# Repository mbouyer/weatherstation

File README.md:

# weatherstation
A home weather station with internet connectivity

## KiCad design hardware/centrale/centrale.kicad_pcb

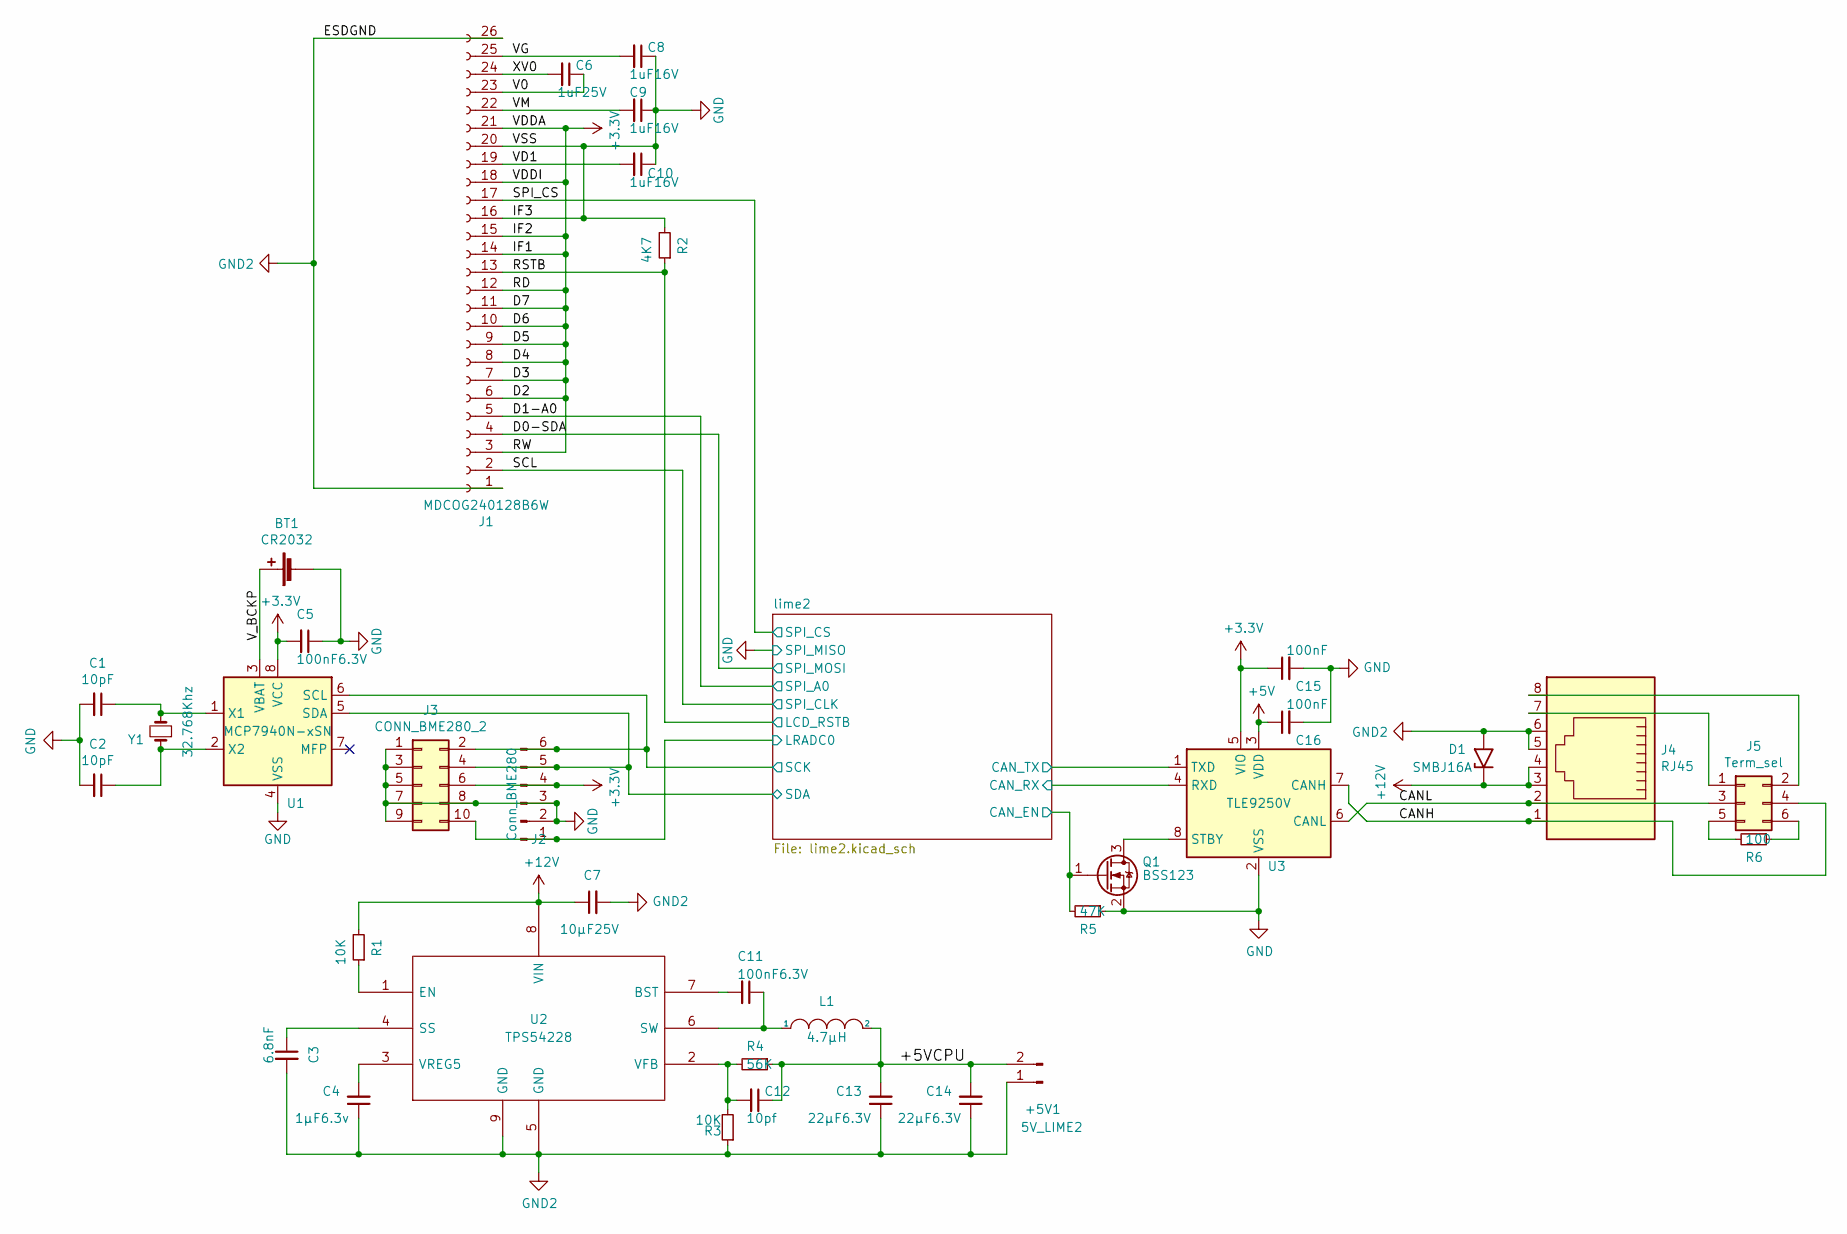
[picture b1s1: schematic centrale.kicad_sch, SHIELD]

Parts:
+5V1: 5V_LIME2; MC24356
BT1: CR2032; 1066
C1, C2: 10pF; C_0603_1608Metric_Pad1.08x0.95mm_HandSolder
C3: 6.8nF; C_0603_1608Metric_Pad1.08x0.95mm_HandSolder
C4: 1µF6.3v; C_0805_2012Metric_Pad1.18x1.45mm_HandSolder
C5, C11: 100nF6.3V; C_0805_2012Metric_Pad1.18x1.45mm_HandSolder
C6: 1uF25V; C_0805_2012Metric_Pad1.18x1.45mm_HandSolder
C7: 10µF25V; C_1210_3225Metric_Pad1.33x2.70mm_HandSolder
C8, C9, C10: 1uF16V; C_0805_2012Metric_Pad1.18x1.45mm_HandSolder
C12: 10pf; C_0603_1608Metric_Pad1.08x0.95mm_HandSolder
C13, C14: 22µF6.3V; C_1210_3225Metric_Pad1.33x2.70mm_HandSolder
C15, C16: 100nF; C_0805_2012Metric_Pad1.18x1.45mm_HandSolder
D1: SMBJ16A; D_SMB_Handsoldering
J1: MDCOG240128B6W; multicomp505110-2691
J2: Conn_BME280; JST_S6B-ZR-SM4A-TF(LF)(SN)
J3: CONN_BME280_2; CONN-TE-MICROMATCH-5X2-PTH-BOSS
J4: RJ45; RJ45_Amphenol_54602-x08_Horizontal
J5: Term_sel; PinHeader_2x03_P2.54mm_Vertical
L1: 4.7µH; L_TT_7.3x6.8
Q1: BSS123; SOT-23
R1, R3: 10K; R_1206_3216Metric_Pad1.30x1.75mm_HandSolder
R2: 4K7; R_0805_2012Metric_Pad1.20x1.40mm_HandSolder
R4: 56K; R_0805_2012Metric_Pad1.20x1.40mm_HandSolder
R5: 47K; R_0805_2012Metric_Pad1.20x1.40mm_HandSolder
R6: 100; R_0805_2012Metric_Pad1.20x1.40mm_HandSolder
U1: MCP7940N-xSN; SOIC-8_3.9x4.9mm_P1.27mm
U2: TPS54228; SOIC-8-1EP_3.9x4.9mm_P1.27mm_EP2.41x3.3mm
U3: TLE9250V; SOIC-8_3.9x4.9mm_P1.27mm
Y1: 32.768Khz; CMR200T

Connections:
+3.3V: C5.2, C15.1, J1.3, J1.6, J1.7, J1.8, J1.9, J1.10, J1.11, J1.12, J1.14, J1.15, J1.18, J1.21, J2.4, J3.6, U1.8 (VCC), U3.5 (VIO); also elsewhere on the board
+5V: C16.1, U3.3 (VDD); also elsewhere on the board
+12V: C7.1, D1.1 (A1), J4.3, J4.4, R1.2, U2.8 (VIN)
/+5VCPU: +5V1.2, C12.1, C13.2, C14.2, L1.2, R4.1
/CANH: J4.1, J5.4, U3.7 (CANH)
/CANL: J4.2, J5.3, U3.6 (CANL)
/D0-SDA: J1.4; also elsewhere on the board
/D1-A0: J1.5; also elsewhere on the board
/RSTB: J1.13, R2.1; also elsewhere on the board
/SCL: J1.2; also elsewhere on the board
/SPI_CS: J1.17; also elsewhere on the board
/V0: C6.1, J1.23
/VD1: C10.2, J1.19
/VG: C8.2, J1.25
/VM: C9.2, J1.22
/V_BCKP: BT1.1 (+), U1.3 (VBAT)
/XV0: C6.2, J1.24
/lime2/EMDC/LCD1_D21/ATADREQ/CAN_RX/EINT21/CSI1_D21/PH21: U3.4 (RXD); also elsewhere on the board
/lime2/ERXDV/LCD1_D20/ATAOE/CAN_TX/EINT20/CSI1_D20/PH20: U3.1 (TXD); also elsewhere on the board
/lime2/ERXERR/LCD1_D19/ATAD15/KP_OUT1/SMC_SDA/EINT19/CSI1_D19/PH19: Q1.1 (G), R5.2; also elsewhere on the board
/lime2/LRADC0: J2.1, J3.10; also elsewhere on the board
/lime2/TWI1_SCK/PB18: J2.6, J3.2, U1.6 (SCL); also elsewhere on the board
/lime2/TWI1_SDA/PB19: J2.5, J3.4, U1.5 (SDA); also elsewhere on the board
GND: BT1.2 (-), C1.2, C2.2, C5.1, C8.1, C9.1, C10.1, C15.2, C16.2, J1.16, J1.20, J2.2, J2.3, J3.1, J3.3, J3.5, J3.7, J3.8, J3.9, Q1.2 (S), R2.2, R5.1, U1.4 (VSS), U3.2 (VSS), U3.9 (VSS); also elsewhere on the board
GND2: +5V1.1, C3.2, C4.1, C7.2, C13.1, C14.1, D1.2 (A2), J1.1, J1.26, J4.5, J4.6, R3.1, U2.5 (GND), U2.9 (GND)
unnamed: C1.1, U1.1 (X1), Y1.2
unnamed: C2.1, U1.2 (X2), Y1.1
unnamed: C3.1, U2.4 (SS)
unnamed: C4.2, U2.3 (VREG5)
unnamed: C11.1, L1.1, U2.6 (SW)
unnamed: C11.2, U2.7 (BST)
unnamed: C12.2, R3.2, R4.2, U2.2 (VFB)
unnamed: J4.7, J5.1
unnamed: J4.8, J5.2
unnamed: J5.5, R6.2
unnamed: J5.6, R6.1
unnamed: Q1.3 (D), U3.8 (STBY)
unnamed: R1.1, U2.1 (EN)

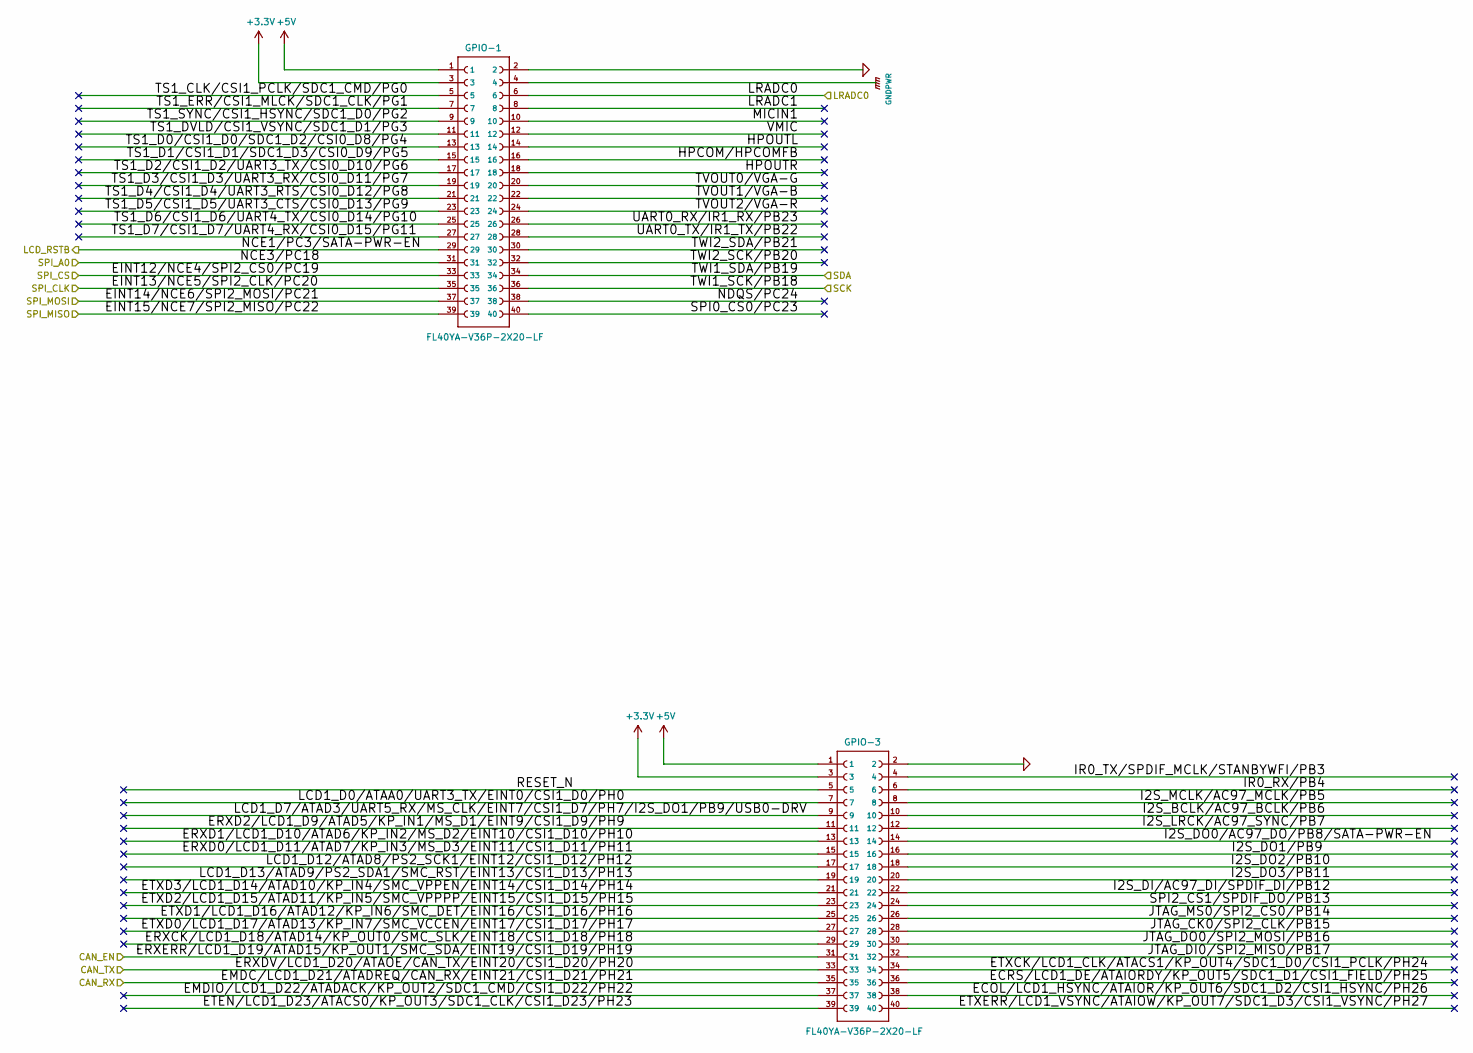
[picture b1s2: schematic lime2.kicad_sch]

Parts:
GPIO-1, GPIO-3: FL40YA-V36P-2X20-LF; A20_OLIMEXINO_LIME2_SHIELD_1-YA-V36P-2X20-LF

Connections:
+3.3V: GPIO-1.3, GPIO-3.3; also elsewhere on the board
+5V: GPIO-1.1, GPIO-3.1; also elsewhere on the board
/D0-SDA: GPIO-1.37; also elsewhere on the board
/D1-A0: GPIO-1.31; also elsewhere on the board
/RSTB: GPIO-1.29; also elsewhere on the board
/SCL: GPIO-1.35; also elsewhere on the board
/SPI_CS: GPIO-1.33; also elsewhere on the board
/lime2/ECOL/LCD1_HSYNC/ATAIOR/KP_OUT6/SDC1_D2/CSI1_HSYNC/PH26: GPIO-3.38
/lime2/ECRS/LCD1_DE/ATAIORDY/KP_OUT5/SDC1_D1/CSI1_FIELD/PH25: GPIO-3.36
/lime2/EMDC/LCD1_D21/ATADREQ/CAN_RX/EINT21/CSI1_D21/PH21: GPIO-3.35; also elsewhere on the board
/lime2/EMDIO/LCD1_D22/ATADACK/KP_OUT2/SDC1_CMD/CSI1_D22/PH22: GPIO-3.37
/lime2/ERXCK/LCD1_D18/ATAD14/KP_OUT0/SMC_SLK/EINT18/CSI1_D18/PH18: GPIO-3.29
/lime2/ERXD0/LCD1_D11/ATAD7/KP_IN3/MS_D3/EINT11/CSI1_D11/PH11: GPIO-3.15
/lime2/ERXD1/LCD1_D10/ATAD6/KP_IN2/MS_D2/EINT10/CSI1_D10/PH10: GPIO-3.13
/lime2/ERXD2/LCD1_D9/ATAD5/KP_IN1/MS_D1/EINT9/CSI1_D9/PH9: GPIO-3.11
/lime2/ERXDV/LCD1_D20/ATAOE/CAN_TX/EINT20/CSI1_D20/PH20: GPIO-3.33; also elsewhere on the board
/lime2/ERXERR/LCD1_D19/ATAD15/KP_OUT1/SMC_SDA/EINT19/CSI1_D19/PH19: GPIO-3.31; also elsewhere on the board
/lime2/ETEN/LCD1_D23/ATACS0/KP_OUT3/SDC1_CLK/CSI1_D23/PH23: GPIO-3.39
/lime2/ETXCK/LCD1_CLK/ATACS1/KP_OUT4/SDC1_D0/CSI1_PCLK/PH24: GPIO-3.34
/lime2/ETXD0/LCD1_D17/ATAD13/KP_IN7/SMC_VCCEN/EINT17/CSI1_D17/PH17: GPIO-3.27
/lime2/ETXD1/LCD1_D16/ATAD12/KP_IN6/SMC_DET/EINT16/CSI1_D16/PH16: GPIO-3.25
/lime2/ETXD2/LCD1_D15/ATAD11/KP_IN5/SMC_VPPPP/EINT15/CSI1_D15/PH15: GPIO-3.23
/lime2/ETXD3/LCD1_D14/ATAD10/KP_IN4/SMC_VPPEN/EINT14/CSI1_D14/PH14: GPIO-3.21
/lime2/ETXERR/LCD1_VSYNC/ATAIOW/KP_OUT7/SDC1_D3/CSI1_VSYNC/PH27: GPIO-3.40
/lime2/HPCOM/HPCOMFB: GPIO-1.16
/lime2/HPOUTL: GPIO-1.14
/lime2/HPOUTR: GPIO-1.18
/lime2/I2S_BCLK/AC97_BCLK/PB6: GPIO-3.10
/lime2/I2S_DI/AC97_DI/SPDIF_DI/PB12: GPIO-3.22
/lime2/I2S_DO0/AC97_DO/PB8/SATA-PWR-EN: GPIO-3.14
/lime2/I2S_DO1/PB9: GPIO-3.16
/lime2/I2S_DO2/PB10: GPIO-3.18
/lime2/I2S_DO3/PB11: GPIO-3.20
/lime2/I2S_LRCK/AC97_SYNC/PB7: GPIO-3.12
/lime2/I2S_MCLK/AC97_MCLK/PB5: GPIO-3.8
/lime2/IR0_RX/PB4: GPIO-3.6
/lime2/IR0_TX/SPDIF_MCLK/STANBYWFI/PB3: GPIO-3.4
/lime2/JTAG_CK0/SPI2_CLK/PB15: GPIO-3.28
/lime2/JTAG_DI0/SPI2_MISO/PB17: GPIO-3.32
/lime2/JTAG_DO0/SPI2_MOSI/PB16: GPIO-3.30
/lime2/JTAG_MS0/SPI2_CS0/PB14: GPIO-3.26
/lime2/LCD1_D0/ATAA0/UART3_TX/EINT0/CSI1_D0/PH0: GPIO-3.7
/lime2/LCD1_D7/ATAD3/UART5_RX/MS_CLK/EINT7/CSI1_D7/PH7/I2S_DO1/PB9/USB0-DRV: GPIO-3.9
/lime2/LCD1_D12/ATAD8/PS2_SCK1/EINT12/CSI1_D12/PH12: GPIO-3.17
/lime2/LCD1_D13/ATAD9/PS2_SDA1/SMC_RST/EINT13/CSI1_D13/PH13: GPIO-3.19
/lime2/LRADC0: GPIO-1.6; also elsewhere on the board
/lime2/LRADC1: GPIO-1.8
/lime2/MICIN1: GPIO-1.10
/lime2/NDQS/PC24: GPIO-1.38
/lime2/RESET_N: GPIO-3.5
/lime2/SPI0_CS0/PC23: GPIO-1.40
/lime2/SPI2_CS1/SPDIF_DO/PB13: GPIO-3.24
/lime2/TS1_CLK/CSI1_PCLK/SDC1_CMD/PG0: GPIO-1.5
/lime2/TS1_D0/CSI1_D0/SDC1_D2/CSI0_D8/PG4: GPIO-1.13
/lime2/TS1_D1/CSI1_D1/SDC1_D3/CSI0_D9/PG5: GPIO-1.15
/lime2/TS1_D2/CSI1_D2/UART3_TX/CSI0_D10/PG6: GPIO-1.17
/lime2/TS1_D3/CSI1_D3/UART3_RX/CSI0_D11/PG7: GPIO-1.19
/lime2/TS1_D4/CSI1_D4/UART3_RTS/CSI0_D12/PG8: GPIO-1.21
/lime2/TS1_D5/CSI1_D5/UART3_CTS/CSI0_D13/PG9: GPIO-1.23
/lime2/TS1_D6/CSI1_D6/UART4_TX/CSI0_D14/PG10: GPIO-1.25
/lime2/TS1_D7/CSI1_D7/UART4_RX/CSI0_D15/PG11: GPIO-1.27
/lime2/TS1_DVLD/CSI1_VSYNC/SDC1_D1/PG3: GPIO-1.11
/lime2/TS1_ERR/CSI1_MLCK/SDC1_CLK/PG1: GPIO-1.7
/lime2/TS1_SYNC/CSI1_HSYNC/SDC1_D0/PG2: GPIO-1.9
/lime2/TVOUT0/VGA-G: GPIO-1.20
/lime2/TVOUT1/VGA-B: GPIO-1.22
/lime2/TVOUT2/VGA-R: GPIO-1.24
/lime2/TWI1_SCK/PB18: GPIO-1.36; also elsewhere on the board
/lime2/TWI1_SDA/PB19: GPIO-1.34; also elsewhere on the board
/lime2/TWI2_SCK/PB20: GPIO-1.32
/lime2/TWI2_SDA/PB21: GPIO-1.30
/lime2/UART0_RX/IR1_RX/PB23: GPIO-1.26
/lime2/UART0_TX/IR1_TX/PB22: GPIO-1.28
/lime2/VMIC: GPIO-1.12
GND: GPIO-1.2, GPIO-1.39, GPIO-3.2; also elsewhere on the board
GNDPWR: GPIO-1.4

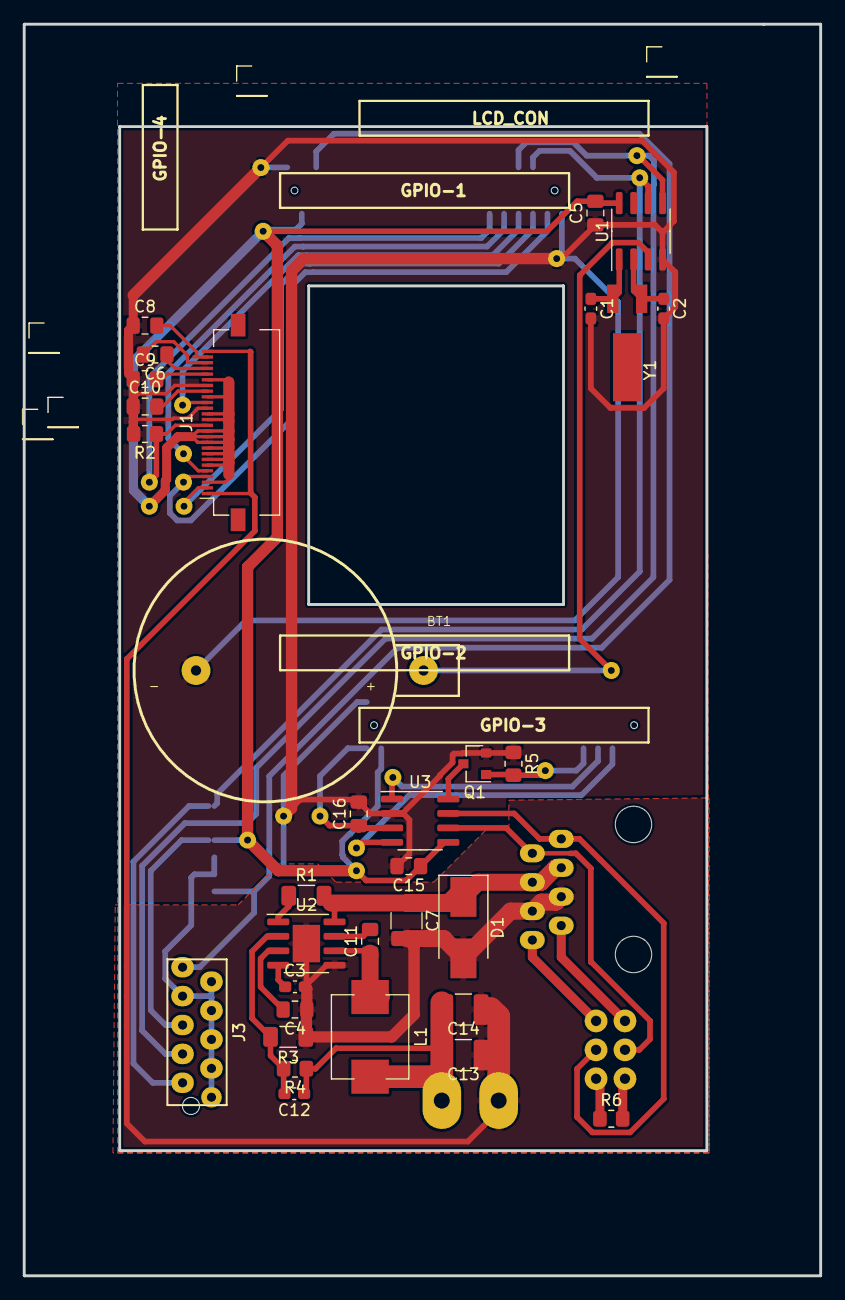
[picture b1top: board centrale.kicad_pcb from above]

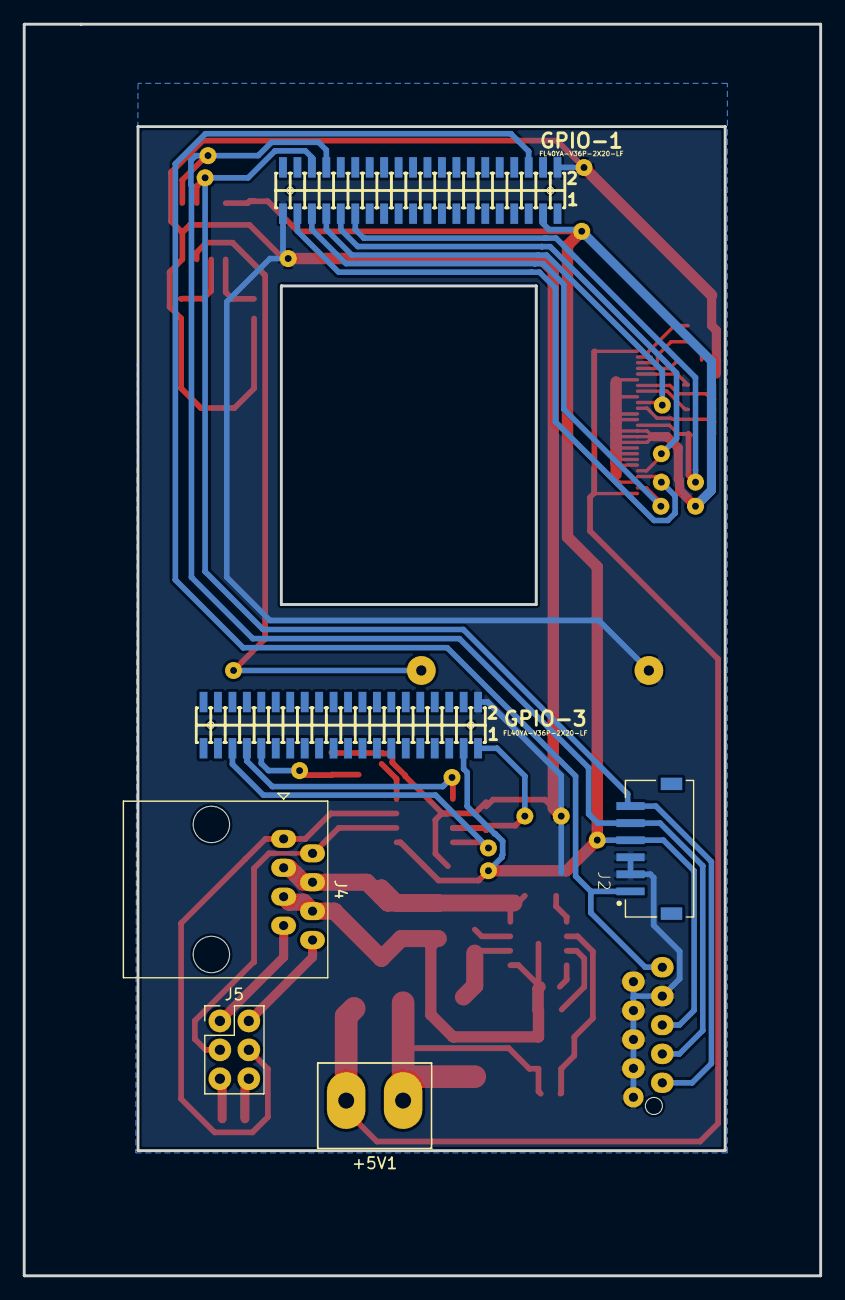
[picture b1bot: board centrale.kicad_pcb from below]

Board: 2 copper layers, 70.0 x 110.0 mm, 38 parts (6 on the bottom side), 38 nets.

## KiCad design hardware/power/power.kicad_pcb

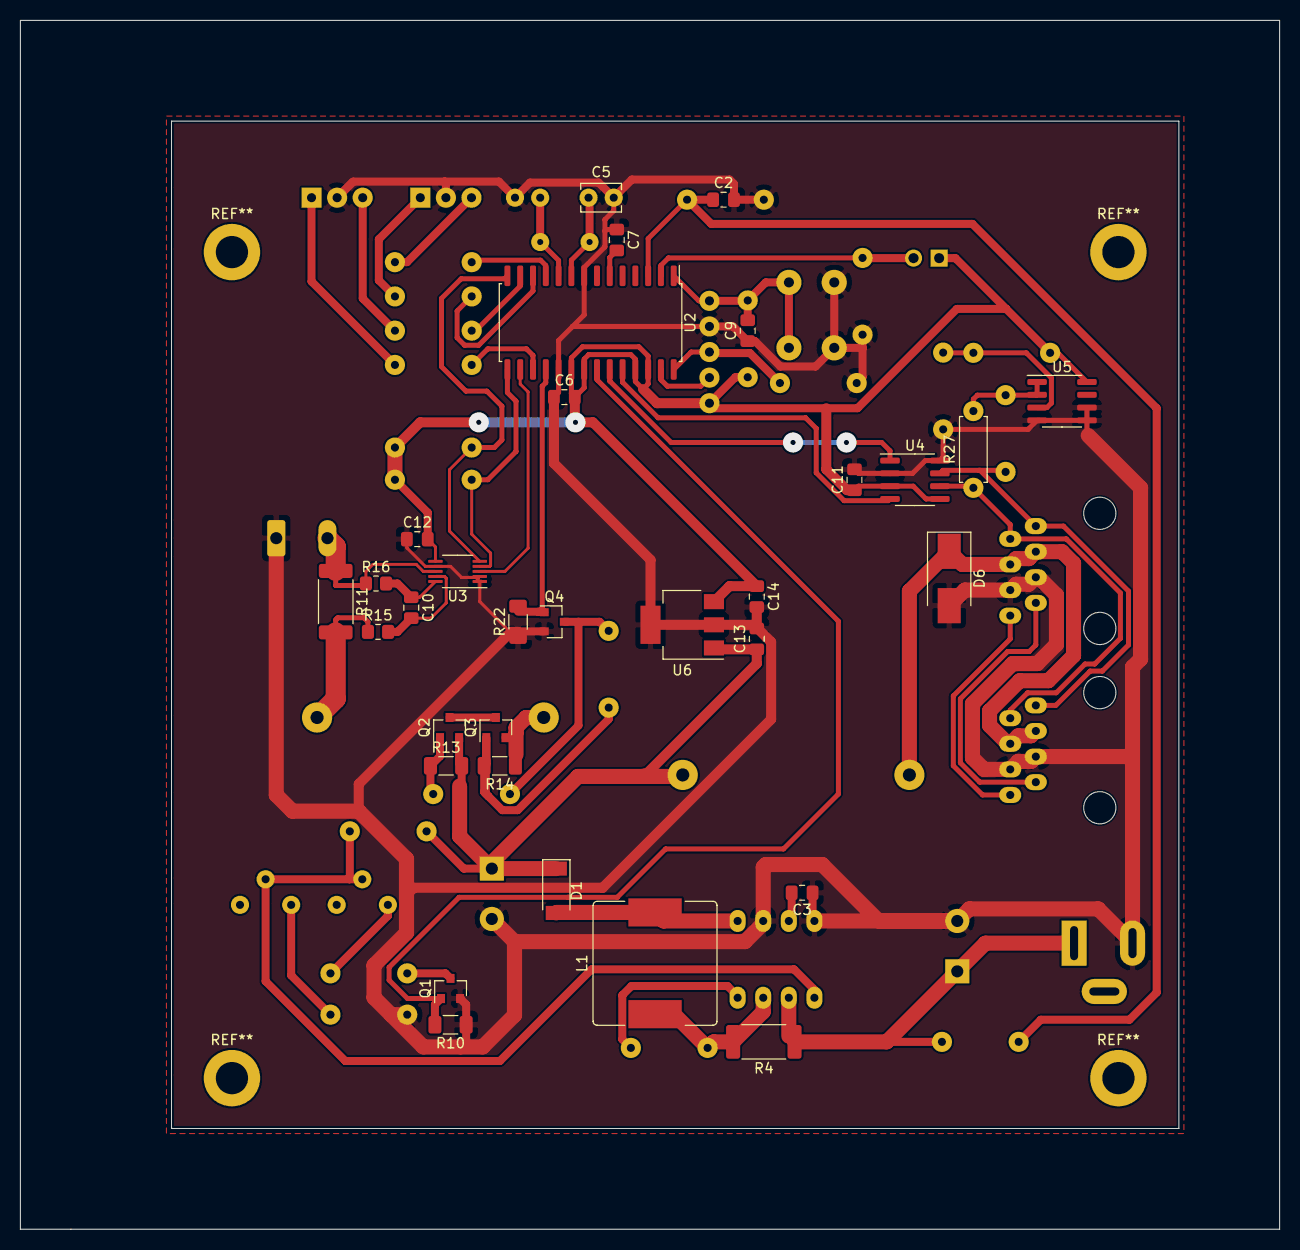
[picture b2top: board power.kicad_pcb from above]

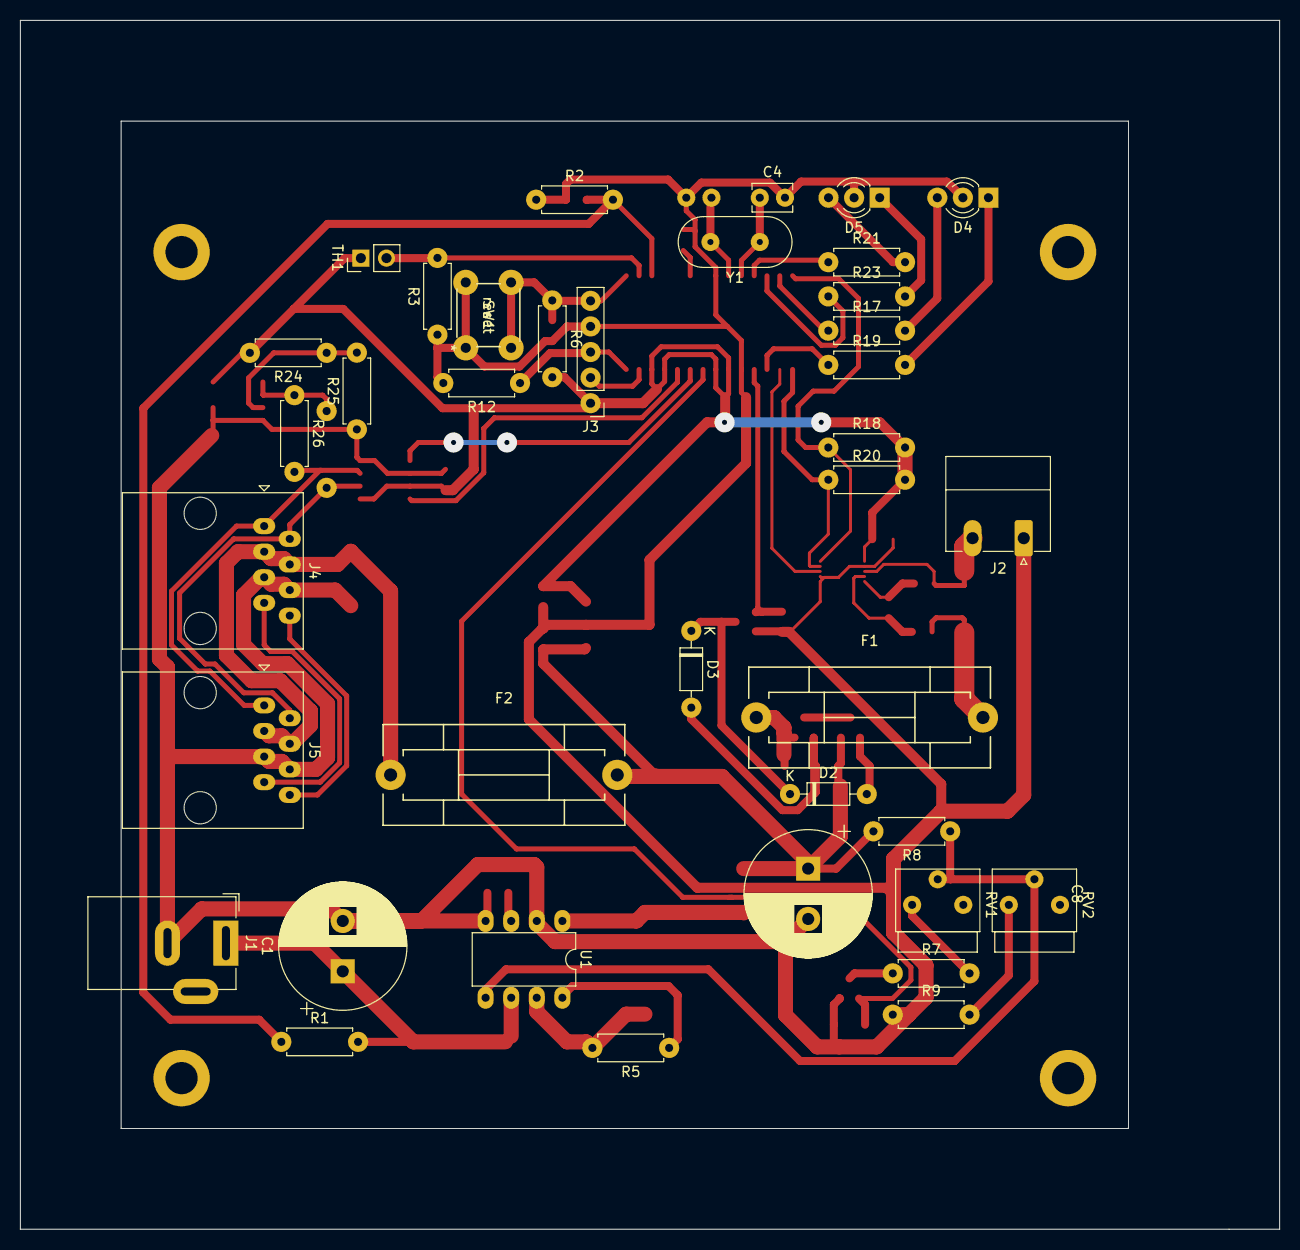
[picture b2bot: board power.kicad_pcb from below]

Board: 2 copper layers, 125.0 x 120.0 mm, 70 parts (38 on the bottom side), 51 nets.

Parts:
C1, C8: 1000µF; CP_Radial_D12.5mm_P5.00mm
C2, C6, C9, C11, C12: 100nF; C_0805_2012Metric_Pad1.18x1.45mm_HandSolder
C3, C10: 1nF; C_0805_2012Metric_Pad1.18x1.45mm_HandSolder
C4, C5: 22pF; C_Disc_D3.8mm_W2.6mm_P2.50mm
C7, C13, C14: 10uF; C_0805_2012Metric_Pad1.18x1.45mm_HandSolder
D1: D_Schottky; D_SOD-128
D2, D3: 1N4148; D_DO-35_SOD27_P7.62mm_Horizontal
D4, D5: LED; LED_D3.0mm-3
D6: SMBJ16A; D_SMB_Handsoldering
F1: 2A; Fuseholder5x20_horiz_SemiClosed_Casing10x22.5mm
F2: 1A; Fuseholder5x20_horiz_SemiClosed_Casing10x22.5mm
J1: Jack-DC; BarrelJack_Wuerth_6941xx301002
J2: BATT; PhoenixContact_MC_1,5_2-G-5.08_1x02_P5.08mm_Horizontal
J3: Conn_01x05_Male; PinHeader_1x05_P2.54mm_Vertical
J4, J5: RJ45; RJ45_Amphenol_54602-x08_Horizontal
L1: 220µH; L_Bourns_SRR1210A
Q1, Q4: BSS123; SOT-23
Q2, Q3: PMOS; SOT-23
R1, R3, R6, R12, R24, R25: 10K; R_Axial_DIN0207_L6.3mm_D2.5mm_P7.62mm_Horizontal
R2, R9: 1.8K; R_Axial_DIN0207_L6.3mm_D2.5mm_P7.62mm_Horizontal
R4: 0.22; R_2512_6332Metric_Pad1.40x3.35mm_HandSolder
R5: 180; R_Axial_DIN0207_L6.3mm_D2.5mm_P7.62mm_Horizontal
R7, R8: 18K7; R_Axial_DIN0207_L6.3mm_D2.5mm_P7.62mm_Horizontal
R10, R13, R14, R22: 10K; R_1206_3216Metric_Pad1.30x1.75mm_HandSolder
R11: 0.039; R_2512_6332Metric_Pad1.40x3.35mm_HandSolder
R15, R16: 10; R_0805_2012Metric_Pad1.20x1.40mm_HandSolder
R17, R19, R21, R23, R26, R27: 330; R_Axial_DIN0207_L6.3mm_D2.5mm_P7.62mm_Horizontal
R18, R20: 4K7; R_Axial_DIN0207_L6.3mm_D2.5mm_P7.62mm_Horizontal
RV1: 100K; Potentiometer_Bourns_3339S_Horizontal
RV2: 500; Potentiometer_Bourns_3339S_Horizontal
SW1: reset; 1825910-7
TH1: NTC10K; PinHeader_1x02_P2.54mm_Vertical
U1: MC33063AP; DIP-8_W7.62mm
U2: PIC18F26K80_ISS; SOIC-28W_7.5x17.9mm_P1.27mm
U3: INA226; VSSOP-10_3x3mm_P0.5mm
U4: MCP2542FDxMF; SOIC-8_3.9x4.9mm_P1.27mm
U5: LM358; SOIC-8_3.9x4.9mm_P1.27mm
U6: uA7805; SOT-223-3_TabPin2
Y1: 10Mhz; Crystal_HC18-U_Vertical

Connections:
+5V: C6.2, C11.1, C12.2, C14.1, J3.1, R6.2, R18.2, R20.2, R24.2, TH1.1, U2.20, U2.21, U2.25, U2.26, U3.6, U4.3, U4.5, U5.8, U6.3
+12V: C8.1, C13.1, D1.1, F2.2, Q2.2, R8.2, R13.2, U6.1
/+BATT: J2.2, R11.1, R16.1, U3.8
/ALRT: U2.16, U3.3
/BATT_ON: Q4.1, R22.2, U2.18
/B_CHRG: Q1.1, R10.2, U2.22
/CANH: J4.1, J5.1, R26.2, U4.7
/CANL: J4.2, J5.2, R27.1, U4.6
/CANRX: U2.24, U4.4
/CANTX: U2.23, U4.1
/MCLR: C9.2, J3.5, R6.1, SW1.3, SW1.4, U2.1
/PGC: J3.2, U2.27
/PGD: J3.3, R12.1, U2.28
/PS_OK: C2.1, R1.1, R2.2, U2.3
/SCL: R18.1, U2.14, U3.5
/SDA: R20.1, U2.15, U3.4
GND: C1.2, C2.2, C3.1, C4.2, C5.2, C6.1, C7.1, C8.2, C9.1, C11.2, C12.1, C13.2, C14.2, D4.2, D5.2, D6.2, J1.2, J2.1, J3.4, J4.5, J4.6, J5.5, J5.6, Q1.2, Q4.2, R2.1, R3.1, R9.1, R10.1, R12.2, R22.1, R25.1, SW1.1, SW1.2, U1.2, U1.4, U2.8, U2.19, U3.1, U3.2, U3.7, U4.2, U4.8, U5.4, U5.5, U5.6, U6.2
unnamed: C1.1, J1.1, R1.2, R4.1, U1.6
unnamed: C3.2, U1.3
unnamed: C4.1, U2.10, Y1.1
unnamed: C5.1, U2.9, Y1.2
unnamed: C7.2, U2.6
unnamed: C10.1, R16.2, U3.10
unnamed: C10.2, R15.2, U3.9
unnamed: D1.2, L1.2, U1.1
unnamed: D2.1, D3.1, Q4.3
unnamed: D2.2, Q2.1, R13.1
unnamed: D3.2, Q3.1, R14.2
unnamed: D4.1, R19.2
unnamed: D4.3, R17.2
unnamed: D5.1, R23.2
unnamed: D5.3, R21.2
unnamed: D6.1, F2.1, J4.3, J4.4, J5.3, J5.4
unnamed: F1.1, Q3.2, R14.1
unnamed: F1.2, R11.2, R15.1
unnamed: J4.7, J5.7
unnamed: J4.8, J5.8
unnamed: L1.1, R4.2, R5.2, U1.7
unnamed: Q1.3, R7.1
unnamed: Q2.3, Q3.3
unnamed: R3.2, TH1.2, U2.2
unnamed: R5.1, U1.8
unnamed: R7.2, RV1.3
unnamed: R8.1, RV1.2, RV2.2, U1.5
unnamed: R9.2, RV2.3
unnamed: R17.1, U2.13
unnamed: R19.1, U2.17
unnamed: R21.1, U2.11
unnamed: R23.1, U2.12
unnamed: R24.1, R25.2, U5.3
unnamed: R26.1, R27.2, U5.1, U5.2

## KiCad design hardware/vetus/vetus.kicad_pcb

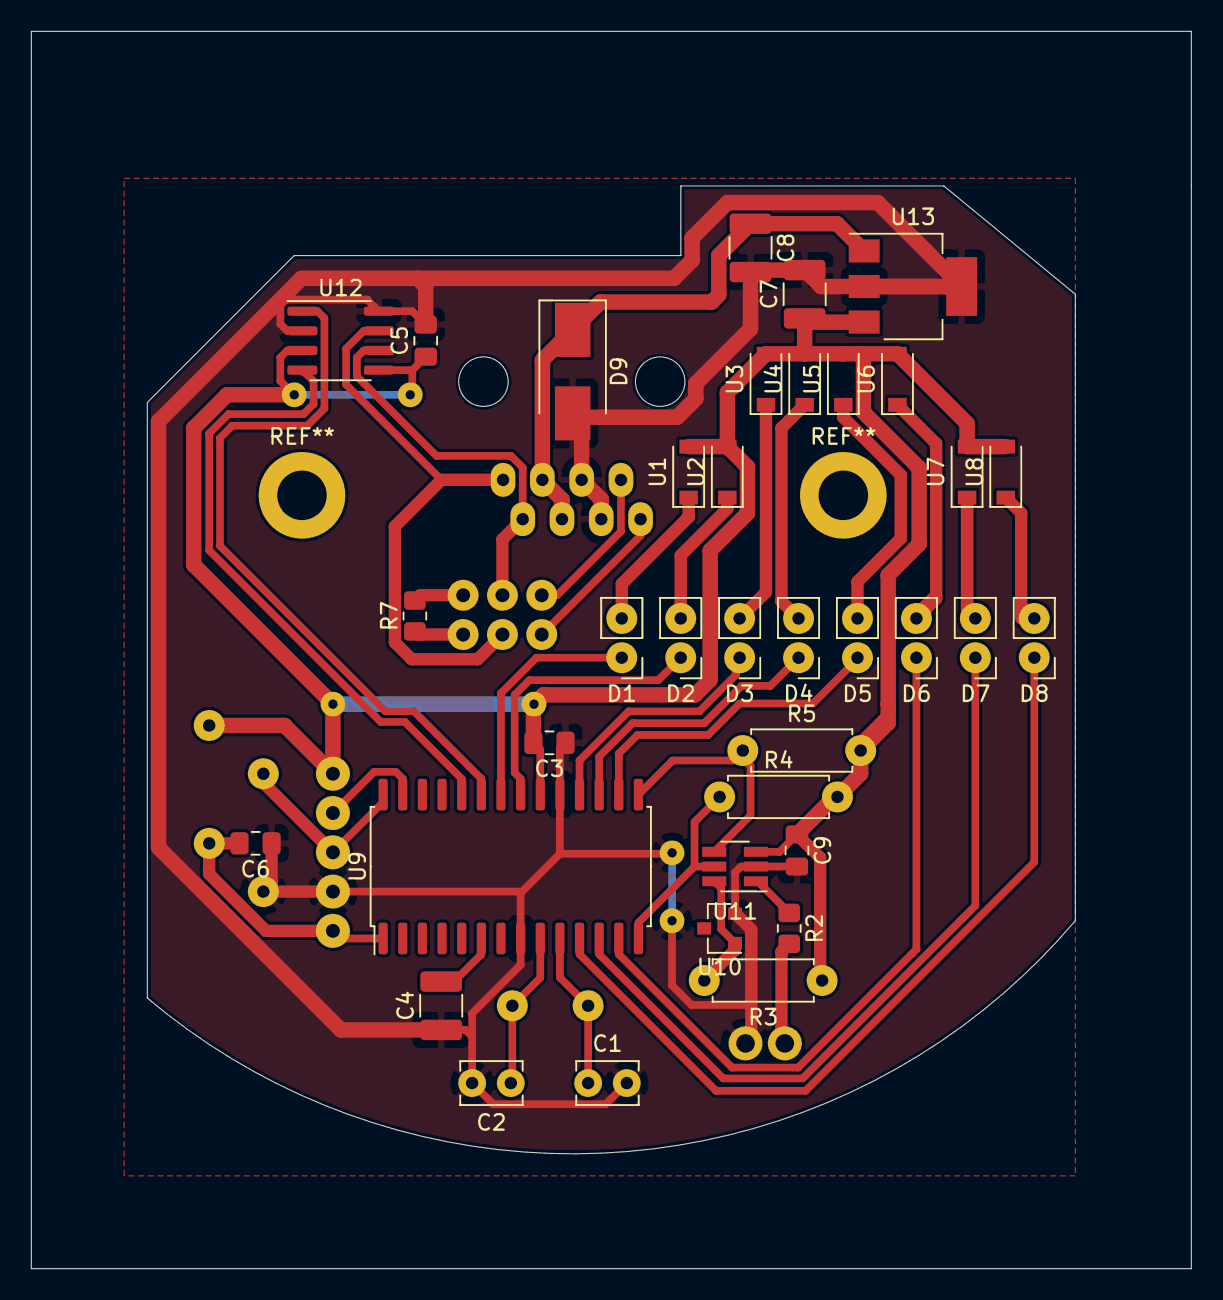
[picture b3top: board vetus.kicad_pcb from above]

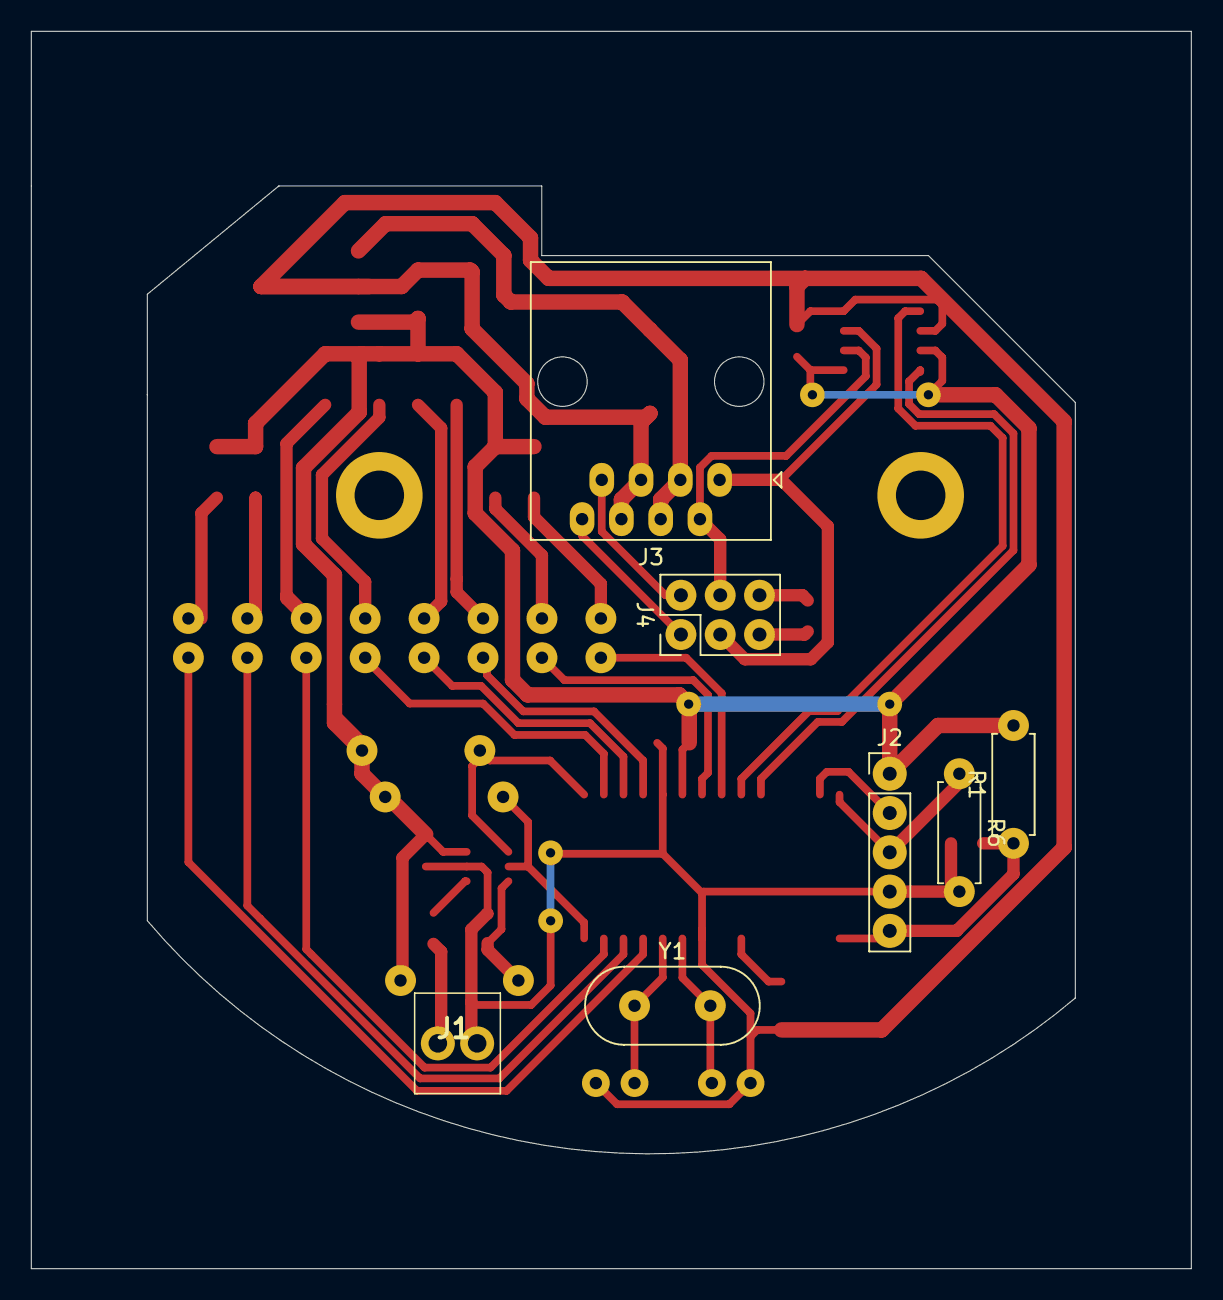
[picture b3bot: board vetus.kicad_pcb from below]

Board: 2 copper layers, 75.0 x 80.0 mm, 43 parts (7 on the bottom side), 38 nets.

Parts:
C1, C2: 22pF; C_Disc_D3.8mm_W2.6mm_P2.50mm
C3, C5, C6, C9: 100nF; C_0805_2012Metric_Pad1.18x1.45mm_HandSolder
C4, C7, C8: 10uF; C_1210_3225Metric_Pad1.33x2.70mm_HandSolder
D1: N; PinHeader_1x02_P2.54mm_Vertical
D2: NE; PinHeader_1x02_P2.54mm_Vertical
D3: E; PinHeader_1x02_P2.54mm_Vertical
D4: SE; PinHeader_1x02_P2.54mm_Vertical
D5: S; PinHeader_1x02_P2.54mm_Vertical
D6: SW; PinHeader_1x02_P2.54mm_Vertical
D7: W; PinHeader_1x02_P2.54mm_Vertical
D8: NW; PinHeader_1x02_P2.54mm_Vertical
D9: SMBJ16A; D_SMB_Handsoldering
J1: anemo; 282834-2_1
J2: Conn_01x05_Male; PinHeader_1x05_P2.54mm_Vertical
J3: RJ45; RJ45_Amphenol_54602-x08_Horizontal
J4: Term_sel; PinHeader_2x03_P2.54mm_Vertical
R1, R6: 10K; R_Axial_DIN0207_L6.3mm_D2.5mm_P7.62mm_Horizontal
R2: 1K74; R_0805_2012Metric_Pad1.20x1.40mm_HandSolder
R3, R4, R5: 4K7; R_Axial_DIN0207_L6.3mm_D2.5mm_P7.62mm_Horizontal
R7: 100; R_0805_2012Metric_Pad1.20x1.40mm_HandSolder
U1, U2, U3, U4, U5, U6, U7, U8: NSI45020T1G; D_SOD-123
U9: PIC18F26K80_ISS; SOIC-28W_7.5x17.9mm_P1.27mm
U10: LM4040DBZ-2.0; SOT-23
U11: MCP4706; SOT-23-6_Handsoldering
U12: MCP2542FDxMF; SOIC-8_3.9x4.9mm_P1.27mm
U13: uA7805; SOT-223-3_TabPin2
Y1: 10Mhz; Crystal_HC18-U_Vertical

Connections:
+5V: C3.2, C5.1, C7.1, C9.1, J2.1, R1.2, R3.1, R4.2, R5.2, U1.2, U2.2, U3.2, U4.2, U5.2, U6.2, U7.2, U8.2, U9.20, U11.3, U12.3, U12.5, U13.3
/+12V: C8.1, D9.1, J3.3, J3.4, U13.1
/CANH: J3.1, J4.3, U12.7
/CANL: J3.2, J4.4, U12.6
/CANRX: U9.24, U12.4
/CANTX: U9.23, U12.1
/E: D3.1, U9.18
/MCLR: C6.2, J2.5, R1.1, U9.1
/N: D1.1, U9.22
/NE: D2.1, U9.21
/NW: D8.1, U9.11
/PGC: J2.2, U9.27
/PGD: J2.3, R6.1, U9.28
/S: D5.1, U9.16
/SCL: R4.1, U9.14, U11.5
/SDA: R5.1, U9.15, U11.4
/SE: D4.1, U9.17
/SW: D6.1, U9.13
/W: D7.1, U9.12
GND: C1.2, C2.2, C3.1, C4.1, C5.2, C6.1, C7.2, C8.2, C9.2, D9.2, J1.2, J2.4, J3.5, J3.6, R6.2, U9.8, U9.19, U10.2, U11.2, U12.2, U12.8, U13.2
unnamed: C1.1, U9.10, Y1.1
unnamed: C2.1, U9.9, Y1.2
unnamed: C4.2, U9.6
unnamed: D1.2, U1.1
unnamed: D2.2, U2.1
unnamed: D3.2, U3.1
unnamed: D4.2, U4.1
unnamed: D5.2, U5.1
unnamed: D6.2, U6.1
unnamed: D7.2, U7.1
unnamed: D8.2, U8.1
unnamed: J1.1, R2.2
unnamed: J3.7, J4.2
unnamed: J3.8, J4.1
unnamed: J4.5, R7.1
unnamed: J4.6, R7.2
unnamed: R2.1, U11.1
unnamed: R3.2, U10.1, U11.6

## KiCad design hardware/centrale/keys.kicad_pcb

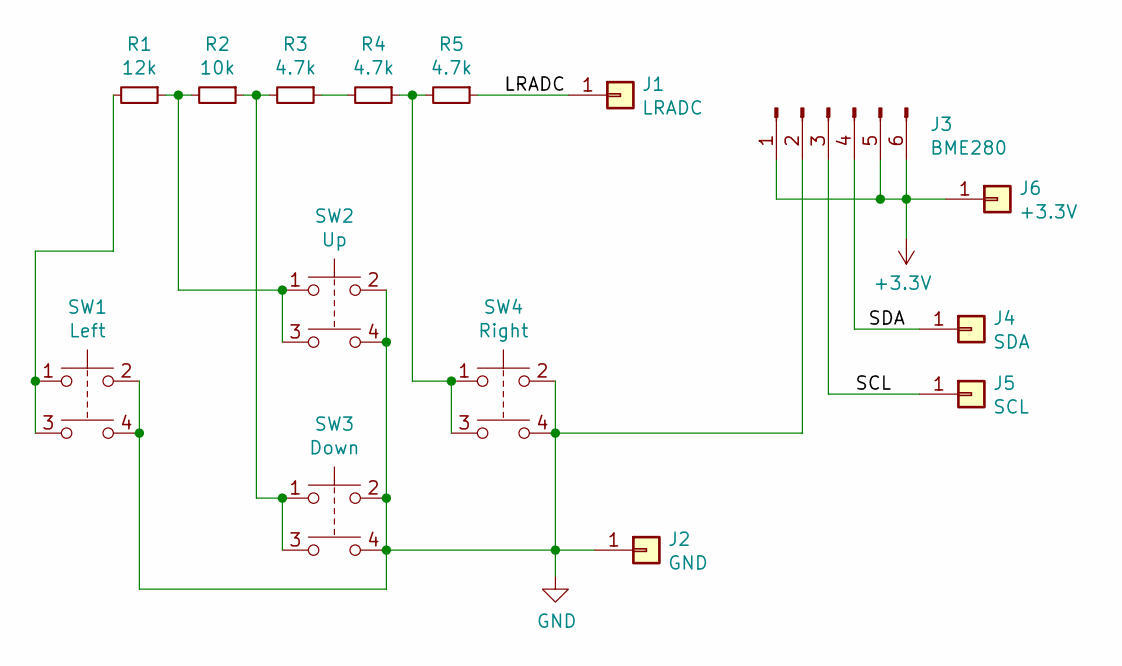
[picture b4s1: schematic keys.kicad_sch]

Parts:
J1: LRADC; SolderWire-0.1sqmm_1x01_D0.4mm_OD1mm_Relief
J2: GND; SolderWire-0.1sqmm_1x01_D0.4mm_OD1mm_Relief
J3: BME280; PinHeader_1x06_P2.54mm_Vertical
J4: SDA; SolderWire-0.1sqmm_1x01_D0.4mm_OD1mm_Relief
J5: SCL; SolderWire-0.1sqmm_1x01_D0.4mm_OD1mm_Relief
J6: +3.3V; SolderWire-0.1sqmm_1x01_D0.4mm_OD1mm_Relief
R1: 12k; R_0805_2012Metric_Pad1.20x1.40mm_HandSolder
R2: 10k; R_0805_2012Metric_Pad1.20x1.40mm_HandSolder
R3, R4, R5: 4.7k; R_0805_2012Metric_Pad1.20x1.40mm_HandSolder
SW1: Left; Push_E-Switch_KS01Q01
SW2: Up; Push_E-Switch_KS01Q01
SW3: Down; Push_E-Switch_KS01Q01
SW4: Right; Push_E-Switch_KS01Q01

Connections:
+3V3: J3.1, J3.5, J3.6, J6.1
/LRADC: J1.1, R5.1
/SCL: J3.3, J5.1
/SDA: J3.4, J4.1
GND: J2.1, J3.2, SW1.2, SW1.4, SW2.2, SW2.4, SW3.2, SW3.4, SW4.2, SW4.4
unnamed: R1.1, R2.2, SW2.1, SW2.3
unnamed: R1.2, SW1.1, SW1.3
unnamed: R2.1, R3.2, SW3.1, SW3.3
unnamed: R3.1, R4.2
unnamed: R4.1, R5.2, SW4.1, SW4.3

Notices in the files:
parts and their libraries:
Copyright 2016 Accelerated Designs. All rights reserved.
